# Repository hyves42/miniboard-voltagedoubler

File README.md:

# miniboard-voltagedoubler
Makes -12V from a 12V input

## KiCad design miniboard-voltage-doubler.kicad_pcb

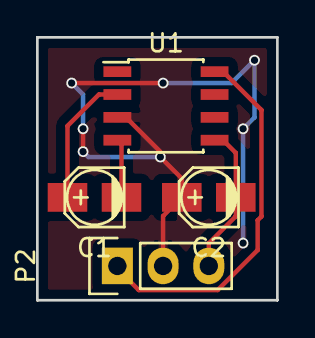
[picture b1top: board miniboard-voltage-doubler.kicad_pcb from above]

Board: 2 copper layers, 13.3 x 14.6 mm, 4 parts (0 on the bottom side), 5 nets.

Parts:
C1, C2: 10uF; c_elec_3x5.3
P2: CONN_01X03; Pin_Header_Straight_1x03
U1: ICL7660; SOIC-8_3.9x4.9mm_Pitch1.27mm

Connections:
GND: C2.1, P2.2, U1.3
unnamed: C1.1, U1.2
unnamed: C1.2, U1.4
VDD: P2.1, U1.8
VEE: C2.2, P2.3, U1.5

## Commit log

2016-02-24 1st version of circuit
2016-02-24 Add picture
